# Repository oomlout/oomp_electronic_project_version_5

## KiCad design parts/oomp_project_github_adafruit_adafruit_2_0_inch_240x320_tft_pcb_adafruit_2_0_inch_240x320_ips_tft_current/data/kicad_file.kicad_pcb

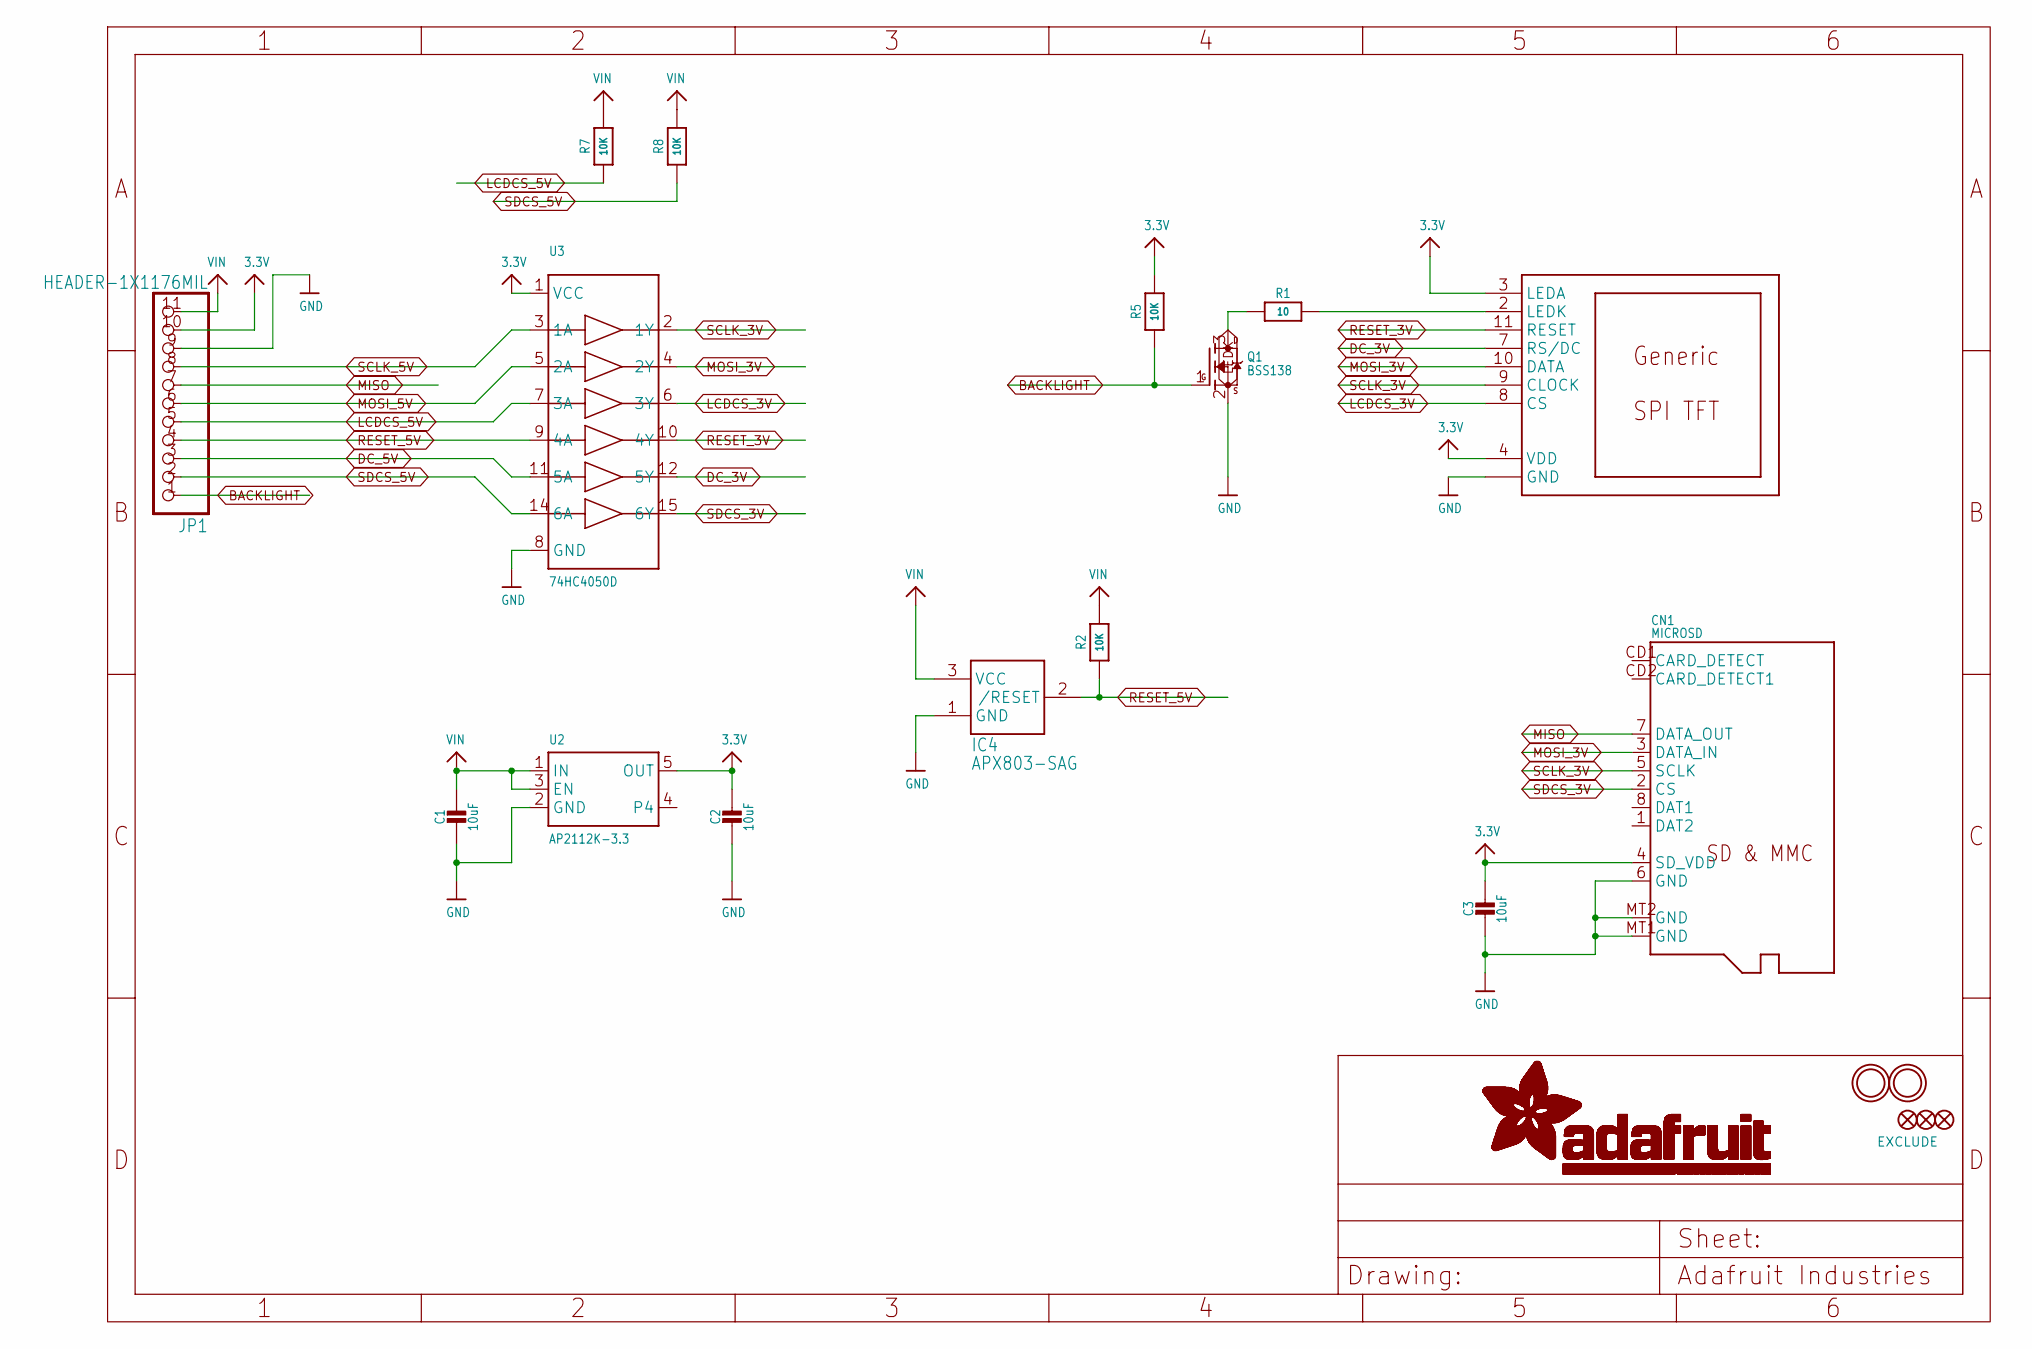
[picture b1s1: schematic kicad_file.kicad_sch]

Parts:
C1, C2, C3: 10uF; 0805-NO
CN1: MICROSD
DISP1: DISP_LCD_GENERIC_SPI_2.0IN_240X320; TFT_2.0IN_240X320_12P
FID1, FID2, FID3: FIDUCIAL_1MM
IC4: APX803-SAG; SOT23
JP1: HEADER-1X1176MIL; 1X11_ROUND_76
Q1: BSS138; SOT23-R
R1: 10; 0805-NO
R2, R5, R7, R8: 10K; 0805-NO
U2: AP2112K-3.3; SOT23-5
U3: 74HC4050D; SOIC16
U$3, U$4: MOUNTINGHOLE2.5; MOUNTINGHOLE_2.5_PLATED

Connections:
3.3V: C2.1, C3.1, CN1.4 (SD_VDD), DISP1.3 (LEDA), DISP1.4 (VDD), JP1.10, R5.2, U2.5 (OUT), U3.1 (VCC)
BACKLIGHT: JP1.1, Q1.1 (G), R5.1
DC_3V: DISP1.7 (RS/DC), U3.12 (5Y)
DC_5V: JP1.3, U3.11 (5A)
GND: C1.2, C2.2, C3.2, CN1.6 (GND), CN1.MT1 (GND), CN1.MT2 (GND), DISP1.1 (GND), DISP1.5 (GND), DISP1.6 (GND), DISP1.12 (GND), IC4.1 (GND), JP1.9, Q1.2 (S), U2.2 (GND), U3.8 (GND)
LCDCS_3V: DISP1.8 (CS), U3.6 (3Y)
LCDCS_5V: JP1.5, R7.1, U3.7 (3A)
LEDK: Q1.3 (D), R1.1
MISO: CN1.7 (DATA_OUT), JP1.7
MOSI_3V: CN1.3 (DATA_IN), DISP1.10 (DATA), U3.4 (2Y)
MOSI_5V: JP1.6, U3.5 (2A)
unnamed: DISP1.2 (LEDK), R1.2
RESET_3V: DISP1.11 (RESET), U3.10 (4Y)
RESET_5V: IC4.2 (/RESET), JP1.4, R2.1, U3.9 (4A)
SCLK_3V: CN1.5 (SCLK), DISP1.9 (CLOCK), U3.2 (1Y)
SCLK_5V: JP1.8, U3.3 (1A)
SDCS_3V: CN1.2 (CS), U3.15 (6Y)
SDCS_5V: JP1.2, R8.1, U3.14 (6A)
VIN: C1.1, IC4.3 (VCC), JP1.11, R2.2, R7.2, R8.2, U2.1 (IN), U2.3 (EN)

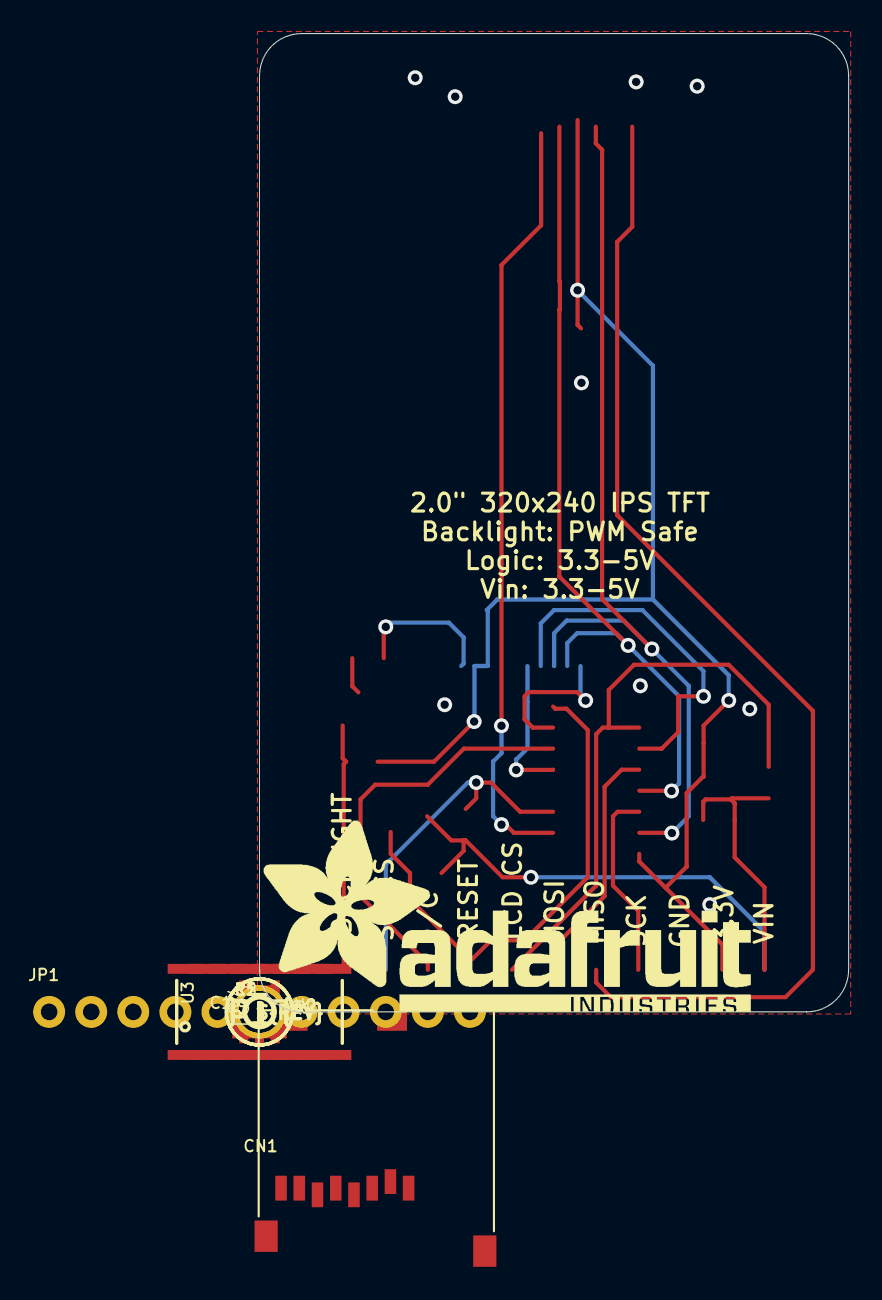
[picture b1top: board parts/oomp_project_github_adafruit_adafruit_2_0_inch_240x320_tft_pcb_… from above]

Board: 2 copper layers, 35.6 x 59.1 mm, 22 parts (1 on the bottom side), 19 nets.

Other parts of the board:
U$20: ADAFRUIT_TEXT_30MM
U$24: PCBFEAT-REV-040

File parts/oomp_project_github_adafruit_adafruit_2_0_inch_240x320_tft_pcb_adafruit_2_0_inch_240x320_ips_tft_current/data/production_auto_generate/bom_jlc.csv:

Comment,Designator,Footprint,LCSC Part #
,JP1,Adafruit 2.0 inch 240x320 IPS TFT-import-fps:1X11_ROUND_76,C2894934
,U$20,Adafruit 2.0 inch 240x320 IPS TFT-import-fps:ADAFRUIT_TEXT_30MM,
,CN1,Adafruit 2.0 inch 240x320 IPS TFT-import-fps:MICROSD,
,U$24,Adafruit 2.0 inch 240x320 IPS TFT-import-fps:PCBFEAT-REV-040,
10,R1,Adafruit 2.0 inch 240x320 IPS TFT-import-fps:0805-NO,C17415
10K,"R2,R5,R7,R8",Adafruit 2.0 inch 240x320 IPS TFT-import-fps:0805-NO,C17414
10uF,"C1,C2,C3",Adafruit 2.0 inch 240x320 IPS TFT-import-fps:0805-NO,
74HC4050D,U3,Adafruit 2.0 inch 240x320 IPS TFT-import-fps:SOIC16,
AP2112K-3.3,U2,Adafruit 2.0 inch 240x320 IPS TFT-import-fps:SOT23-5,
APX803-SAG,IC4,Adafruit 2.0 inch 240x320 IPS TFT-import-fps:SOT23,
BSS138,Q1,Adafruit 2.0 inch 240x320 IPS TFT-import-fps:SOT23-R,C52895
DISP_LCD_GENERIC_SPI_2.0IN_240X320,DISP1,Adafruit 2.0 inch 240x320 IPS TFT-import-fps:TFT_2.0IN_240X320_12P,

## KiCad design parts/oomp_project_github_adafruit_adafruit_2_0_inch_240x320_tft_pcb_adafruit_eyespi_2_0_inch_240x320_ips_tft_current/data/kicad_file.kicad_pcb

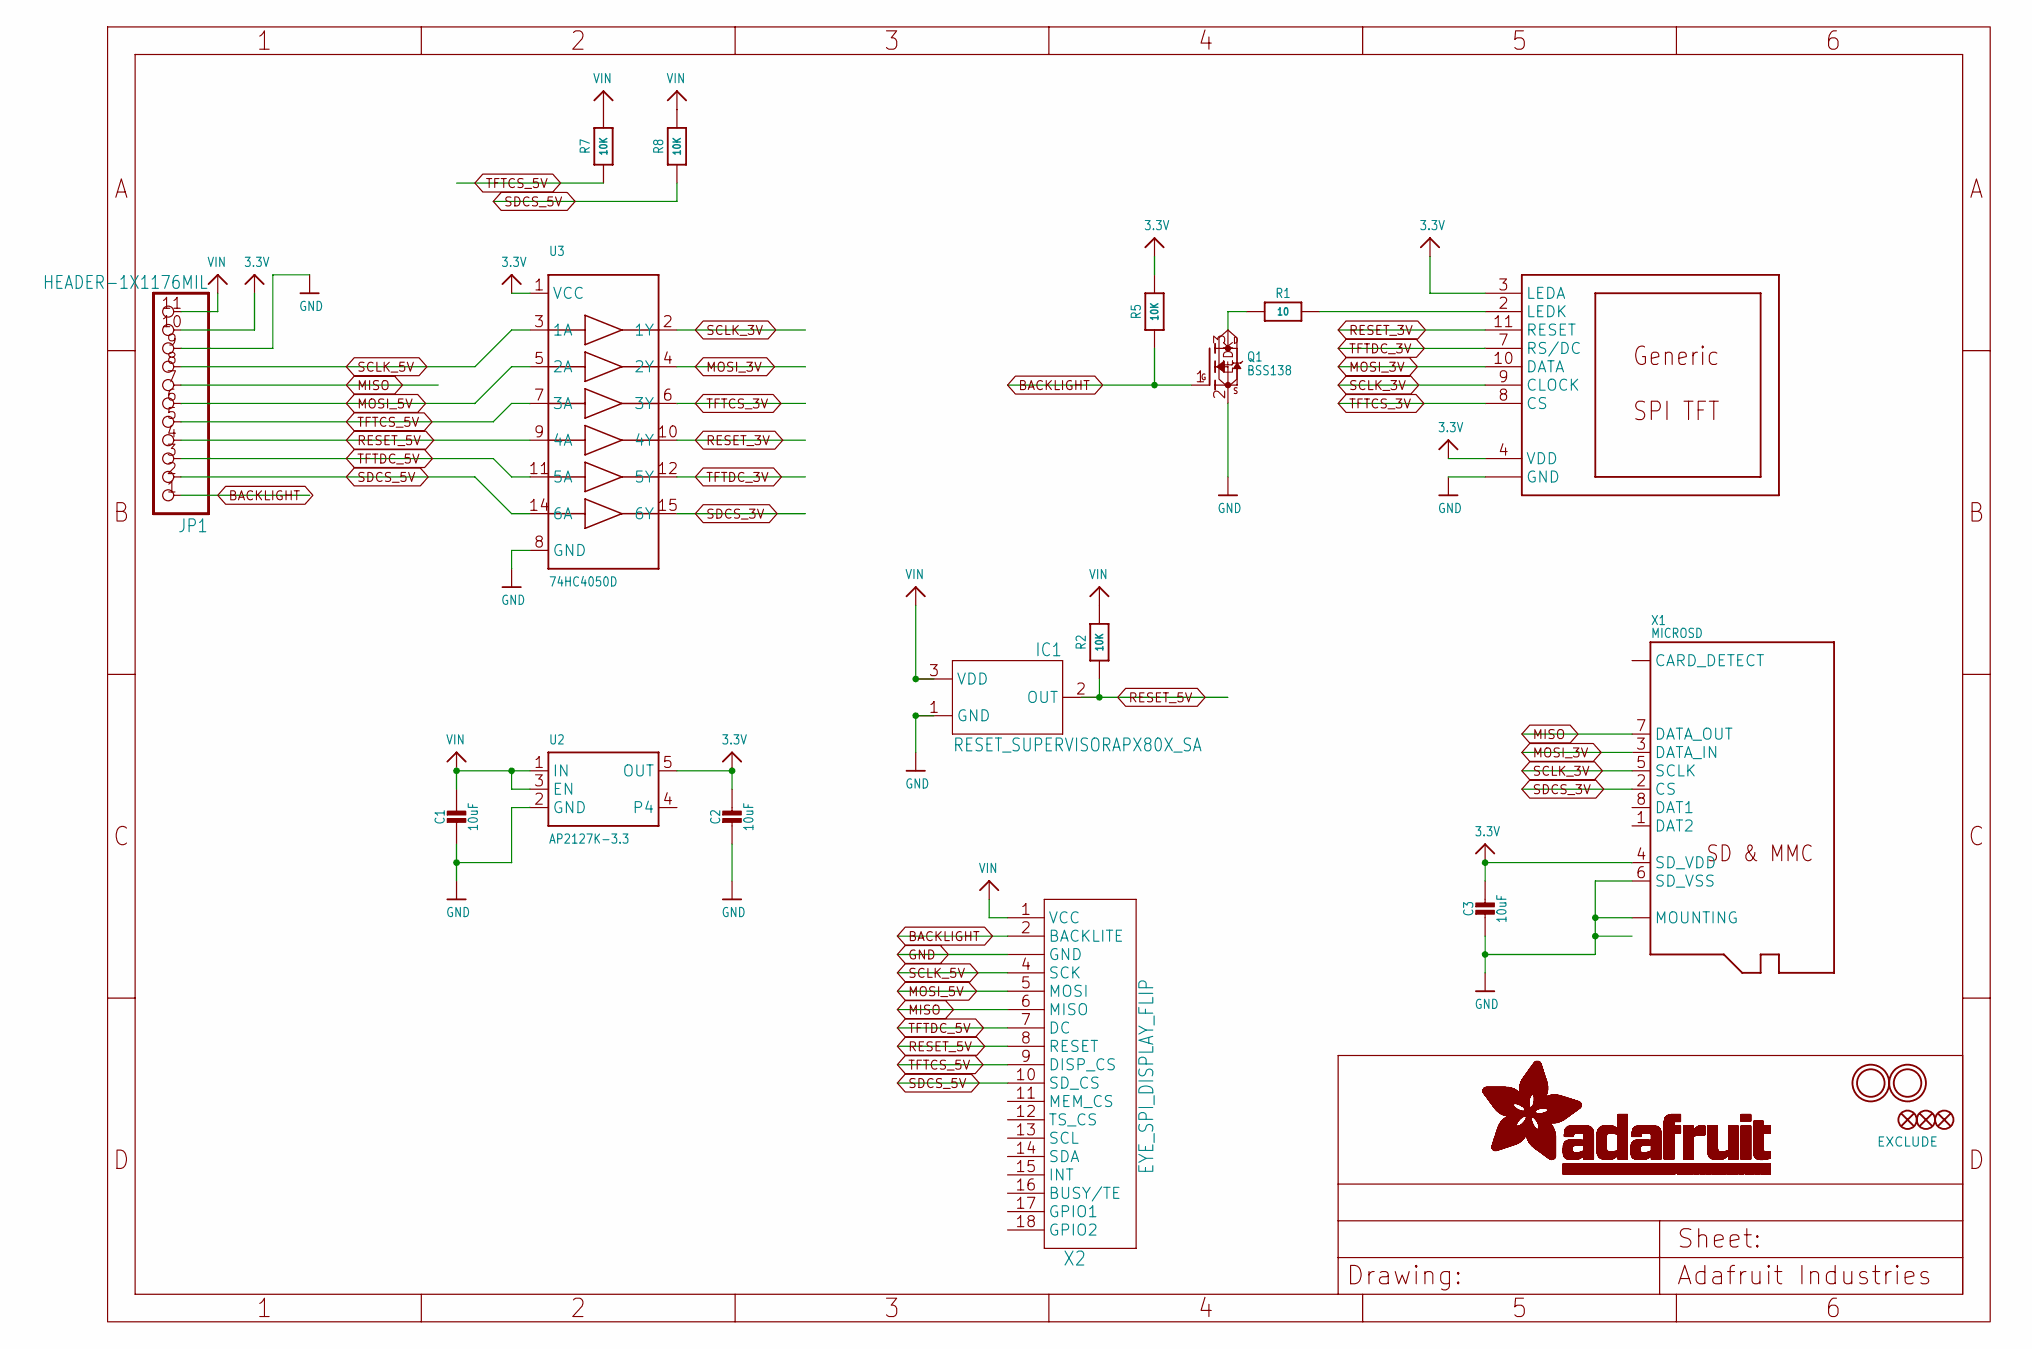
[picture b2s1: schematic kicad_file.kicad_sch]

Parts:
C1, C2, C3: 10uF; 0805-NO
DISP1: DISP_LCD_GENERIC_SPI_2.0IN_240X320; TFT_2.0IN_240X320_12P
FID1, FID2, FID3: FIDUCIAL_1MM
IC1: RESET_SUPERVISORAPX80X_SA; SOT23-WIDE
JP1: HEADER-1X1176MIL; 1X11_ROUND_76
Q1: BSS138; SOT23-R
R1: 10; 0805-NO
R2, R5, R7, R8: 10K; 0805-NO
U2: AP2127K-3.3; SOT23-5; JLC_ROTATION 270
U3: 74HC4050D; SOIC16
U$3, U$4: MOUNTINGHOLE2.5; MOUNTINGHOLE_2.5_PLATED
X1: MICROSD; JLC_ROTATION 90
X2: EYE_SPI_DISPLAY_FLIP; EYE_SPI_DISPLAY_BOTCONTACT; LCSC C2856802

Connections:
3.3V: C2.1, C3.1, DISP1.3 (LEDA), DISP1.4 (VDD), JP1.10, R5.2, U2.5 (OUT), U3.1 (VCC), X1.4 (SD_VDD)
BACKLIGHT: JP1.1, Q1.1 (G), R5.1, X2.2 (BACKLITE)
GND: C1.2, C2.2, C3.2, DISP1.1 (GND), DISP1.5 (GND), DISP1.6 (GND), DISP1.12 (GND), IC1.1 (GND), JP1.9, Q1.2 (S), U2.2 (GND), U3.8 (GND), X1.6 (SD_VSS), X1.MT1 (MOUNTING), X1.MT2 (MOUNTING), X2.3 (GND), X2.SUPPORT1 (GND), X2.SUPPORT2 (GND)
LEDK: Q1.3 (D), R1.1
MISO: JP1.7, X1.7 (DATA_OUT), X2.6 (MISO)
MOSI_3V: DISP1.10 (DATA), U3.4 (2Y), X1.3 (DATA_IN)
MOSI_5V: JP1.6, U3.5 (2A), X2.5 (MOSI)
unnamed: DISP1.2 (LEDK), R1.2
RESET_3V: DISP1.11 (RESET), U3.10 (4Y)
RESET_5V: IC1.2 (OUT), JP1.4, R2.1, U3.9 (4A), X2.8 (RESET)
SCLK_3V: DISP1.9 (CLOCK), U3.2 (1Y), X1.5 (SCLK)
SCLK_5V: JP1.8, U3.3 (1A), X2.4 (SCK)
SDCS_3V: U3.15 (6Y), X1.2 (CS)
SDCS_5V: JP1.2, R8.1, U3.14 (6A), X2.10 (SD_CS)
TFTCS_3V: DISP1.8 (CS), U3.6 (3Y)
TFTCS_5V: JP1.5, R7.1, U3.7 (3A), X2.9 (DISP_CS)
TFTDC_3V: DISP1.7 (RS/DC), U3.12 (5Y)
TFTDC_5V: JP1.3, U3.11 (5A), X2.7 (DC)
VIN: C1.1, IC1.3 (VDD), JP1.11, R2.2, R7.2, R8.2, U2.1 (IN), U2.3 (EN), X2.1 (VCC)

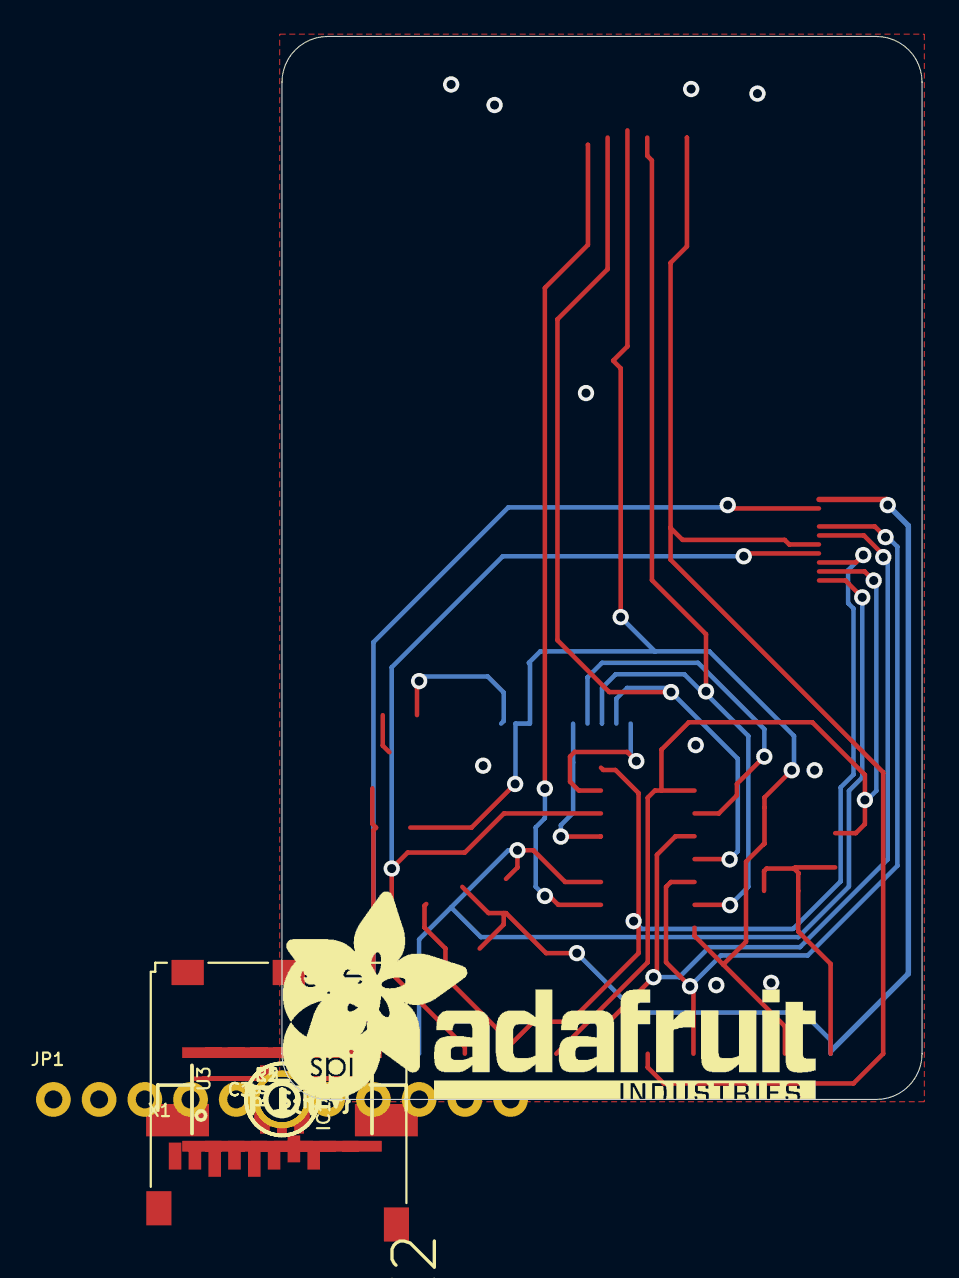
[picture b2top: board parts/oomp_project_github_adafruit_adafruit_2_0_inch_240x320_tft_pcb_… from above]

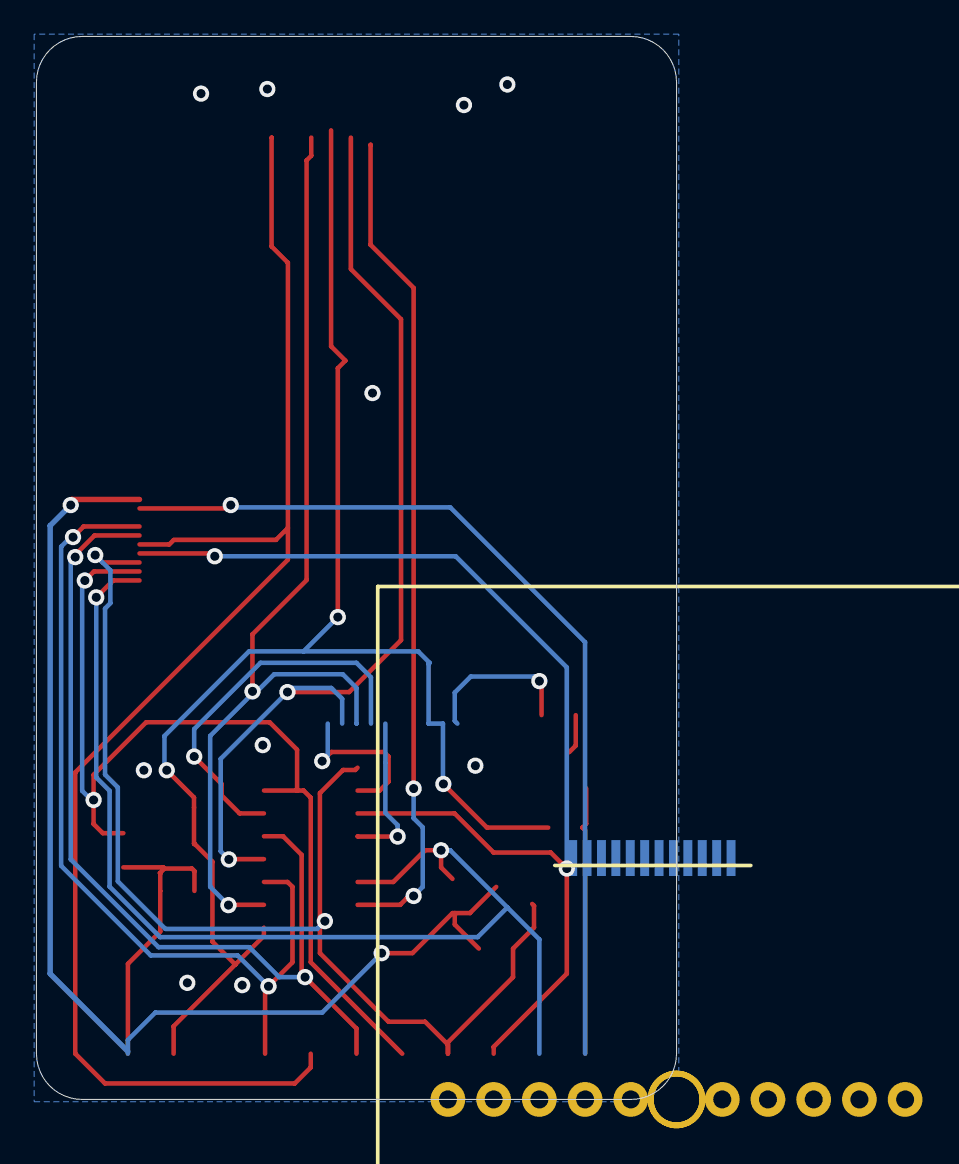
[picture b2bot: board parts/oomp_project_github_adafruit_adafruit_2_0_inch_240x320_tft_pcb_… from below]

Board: 2 copper layers, 35.6 x 59.1 mm, 48 parts (13 on the bottom side), 19 nets.

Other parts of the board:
PLABEL0: PLABEL0
PLABEL1: PLABEL1
PLABEL2: PLABEL2
PLABEL3: PLABEL3
PLABEL4: PLABEL4
PLABEL5: PLABEL5
PLABEL6: PLABEL6
PLABEL7: PLABEL7
PLABEL8: PLABEL8
PLABEL9: PLABEL9
PLABEL10: PLABEL10
PLABEL11: PLABEL11
PLABEL12: PLABEL12
PLABEL13: PLABEL13
PLABEL14: PLABEL14
PLABEL15: PLABEL15
PLABEL16: PLABEL16
PLABEL17: PLABEL17
PLABEL18: PLABEL18
PLABEL19: PLABEL19
PLABEL20: PLABEL20
PLABEL21: PLABEL21
PLABEL22: PLABEL22
PLABEL23: PLABEL23
U$20: ADAFRUIT_TEXT_30MM
U$24: PCBFEAT-REV-040
U$28: EYESPI_MINI_LOGO

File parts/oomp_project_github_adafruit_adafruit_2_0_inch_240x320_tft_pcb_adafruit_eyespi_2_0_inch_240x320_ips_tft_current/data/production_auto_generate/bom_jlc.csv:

Comment,Designator,Footprint,LCSC Part #
,JP1,Adafruit EYESPI 2.0 Inch 240x320 IPS TFT-import-fps:1X11_ROUND_76,C2894934
,U$20,Adafruit EYESPI 2.0 Inch 240x320 IPS TFT-import-fps:ADAFRUIT_TEXT_30MM,
,U$28,Adafruit EYESPI 2.0 Inch 240x320 IPS TFT-import-fps:EYESPI_MINI_LOGO,
,U$24,Adafruit EYESPI 2.0 Inch 240x320 IPS TFT-import-fps:PCBFEAT-REV-040,
,PLABEL0,Adafruit EYESPI 2.0 Inch 240x320 IPS TFT-import-fps:PLABEL0,
,PLABEL1,Adafruit EYESPI 2.0 Inch 240x320 IPS TFT-import-fps:PLABEL1,
,PLABEL10,Adafruit EYESPI 2.0 Inch 240x320 IPS TFT-import-fps:PLABEL10,
,PLABEL11,Adafruit EYESPI 2.0 Inch 240x320 IPS TFT-import-fps:PLABEL11,
,PLABEL12,Adafruit EYESPI 2.0 Inch 240x320 IPS TFT-import-fps:PLABEL12,
,PLABEL13,Adafruit EYESPI 2.0 Inch 240x320 IPS TFT-import-fps:PLABEL13,
,PLABEL14,Adafruit EYESPI 2.0 Inch 240x320 IPS TFT-import-fps:PLABEL14,
,PLABEL15,Adafruit EYESPI 2.0 Inch 240x320 IPS TFT-import-fps:PLABEL15,
,PLABEL16,Adafruit EYESPI 2.0 Inch 240x320 IPS TFT-import-fps:PLABEL16,
,PLABEL17,Adafruit EYESPI 2.0 Inch 240x320 IPS TFT-import-fps:PLABEL17,
,PLABEL18,Adafruit EYESPI 2.0 Inch 240x320 IPS TFT-import-fps:PLABEL18,
,PLABEL19,Adafruit EYESPI 2.0 Inch 240x320 IPS TFT-import-fps:PLABEL19,
,PLABEL2,Adafruit EYESPI 2.0 Inch 240x320 IPS TFT-import-fps:PLABEL2,
,PLABEL20,Adafruit EYESPI 2.0 Inch 240x320 IPS TFT-import-fps:PLABEL20,
,PLABEL21,Adafruit EYESPI 2.0 Inch 240x320 IPS TFT-import-fps:PLABEL21,
,PLABEL22,Adafruit EYESPI 2.0 Inch 240x320 IPS TFT-import-fps:PLABEL22,
,PLABEL23,Adafruit EYESPI 2.0 Inch 240x320 IPS TFT-import-fps:PLABEL23,
,PLABEL3,Adafruit EYESPI 2.0 Inch 240x320 IPS TFT-import-fps:PLABEL3,
,PLABEL4,Adafruit EYESPI 2.0 Inch 240x320 IPS TFT-import-fps:PLABEL4,
,PLABEL5,Adafruit EYESPI 2.0 Inch 240x320 IPS TFT-import-fps:PLABEL5,
,PLABEL6,Adafruit EYESPI 2.0 Inch 240x320 IPS TFT-import-fps:PLABEL6,
,PLABEL7,Adafruit EYESPI 2.0 Inch 240x320 IPS TFT-import-fps:PLABEL7,
,PLABEL8,Adafruit EYESPI 2.0 Inch 240x320 IPS TFT-import-fps:PLABEL8,
,PLABEL9,Adafruit EYESPI 2.0 Inch 240x320 IPS TFT-import-fps:PLABEL9,
10,R1,Adafruit EYESPI 2.0 Inch 240x320 IPS TFT-import-fps:0805-NO,C17415
10K,"R2,R5,R7,R8",Adafruit EYESPI 2.0 Inch 240x320 IPS TFT-import-fps:0805-NO,C17414
10uF,"C1,C2,C3",Adafruit EYESPI 2.0 Inch 240x320 IPS TFT-import-fps:0805-NO,
74HC4050D,U3,Adafruit EYESPI 2.0 Inch 240x320 IPS TFT-import-fps:SOIC16,
AP2127K-3.3,U2,Adafruit EYESPI 2.0 Inch 240x320 IPS TFT-import-fps:SOT23-5,
BSS138,Q1,Adafruit EYESPI 2.0 Inch 240x320 IPS TFT-import-fps:SOT23-R,C52895
DISP_LCD_GENERIC_SPI_2.0IN_240X320,DISP1,Adafruit EYESPI 2.0 Inch 240x320 IPS TFT-import-fps:TFT_2.0IN_240X320_12P,
EYE_SPI_DISPLAY_FLIP,X2,Adafruit EYESPI 2.0 Inch 240x320 IPS TFT-import-fps:EYE_SPI_DISPLAY_BOTCONTACT,
MICROSD,X1,Adafruit EYESPI 2.0 Inch 240x320 IPS TFT-import-fps:MICROSD,
RESET_SUPERVISORAPX80X_SA,IC1,Adafruit EYESPI 2.0 Inch 240x320 IPS TFT-import-fps:SOT23-WIDE,

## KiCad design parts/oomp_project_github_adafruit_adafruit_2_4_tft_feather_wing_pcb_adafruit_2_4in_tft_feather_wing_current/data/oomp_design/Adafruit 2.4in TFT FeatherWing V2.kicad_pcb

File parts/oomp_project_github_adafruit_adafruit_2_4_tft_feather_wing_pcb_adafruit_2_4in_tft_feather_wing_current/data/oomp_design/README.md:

# OOMP KiCad design copy

Open `Adafruit 2.4in TFT FeatherWing V2.kicad_pro` (or the `.kicad_pcb` / `.kicad_sch`) in KiCad. Local OOMP libraries are under `libraries/`. Original inputs are preserved in [../original/](../original/).

Only verified unchanged installed KiCad defaults were renamed. Modified, custom, unmatched and unavailable items remain unchanged. Soldering variants are never swapped during conversion. Existing pad coordinates, nets and UUIDs are preserved.

See [conversion_report.yaml](conversion_report.yaml) for every conversion and skip. Copy this directory before editing; regeneration refuses to overwrite edited design files.

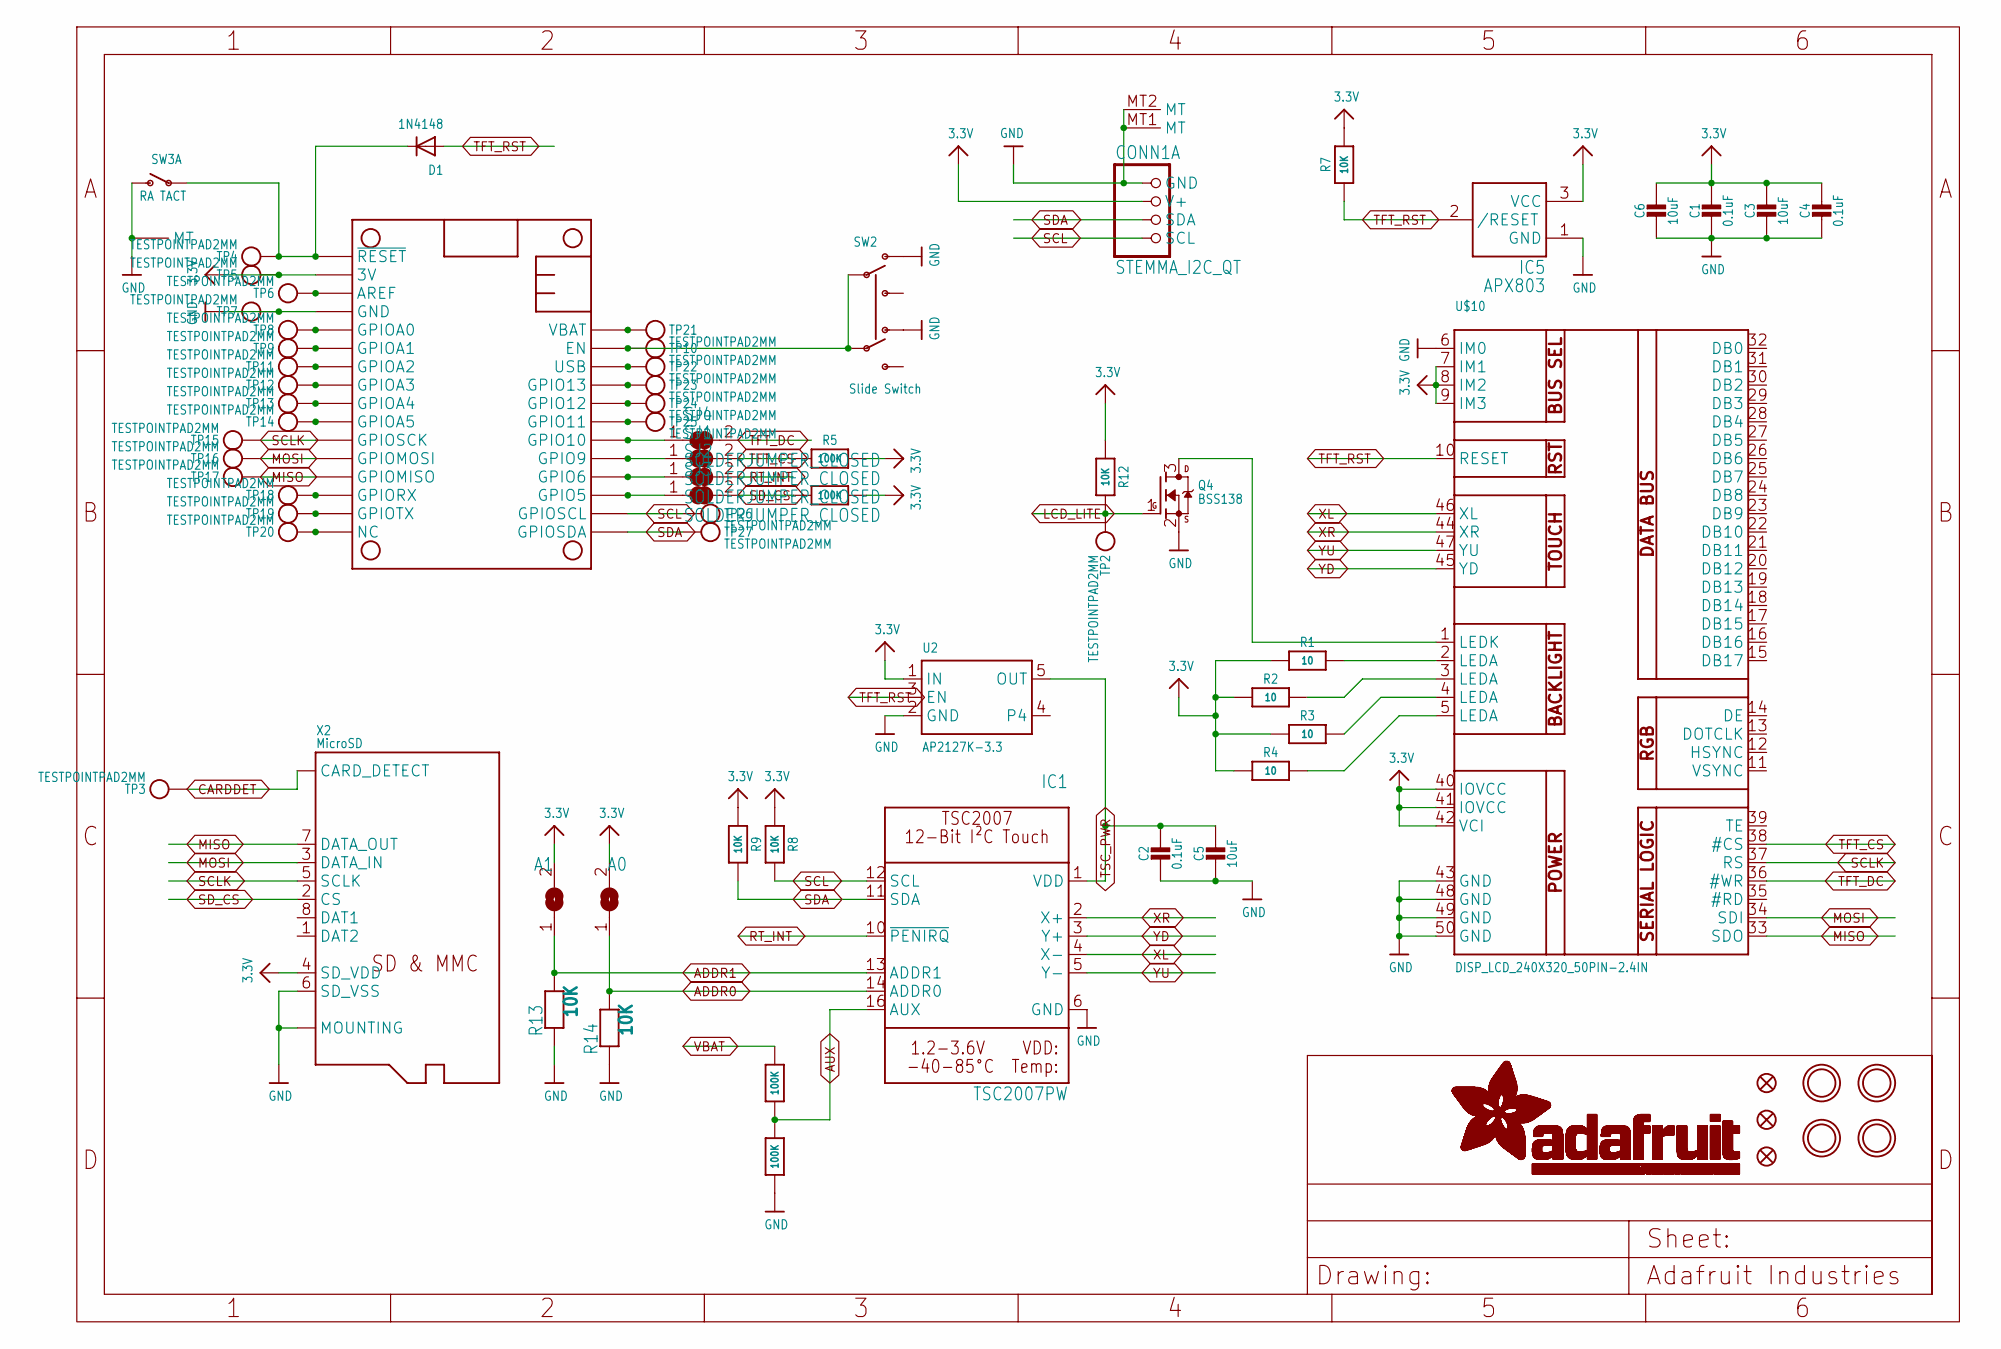
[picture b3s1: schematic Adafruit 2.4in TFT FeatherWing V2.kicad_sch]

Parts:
C1, C2, C4: 0.1uF; 0603-NO
C3, C5, C6: 10uF; 0805-NO
CONN1: STEMMA_I2C_QT; JST_SH4; LCSC C2845363
D1: 1N4148; SOD-323
FID1, FID2, FID3: FIDUCIAL_1MM
IC1: TSC2007PW; TSSOP16
IC5: APX803; SOT23
ICSP_CLK1: A1; SOLDERJUMPER_ARROW_NOPASTE
ICSP_CLK2: A0; SOLDERJUMPER_ARROW_NOPASTE
MS2: FEATHERWING_SMTDUAL; FEATHERWING_SMT2
Q4: BSS138; SOT23-WIDE
R1, R2, R3, R4: 10; 0603-NO
R5, R6, R10, R11: 100K; 0603-NO
R7, R8, R9, R12, R13, R14: 10K; 0603-NO
SJ1, SJ2, SJ3, SJ4: SOLDERJUMPER_CLOSED; SOLDERJUMPER_CLOSEDWIRE
SW2: Slide Switch; EG1390; LCSC C2837066
SW3: RA TACT; SPST_TACTILE_RA; LCSC C778159
TP2, TP3, TP4, TP5, TP6, TP7, TP8, TP9, TP10, TP11, TP12, TP13, TP14, TP15, TP16, TP17, TP18, TP19, TP20, TP21, TP22, TP23, TP24, TP25, TP26, TP27: TESTPOINTPAD2MM; TESTPOINT_PAD_2MM
U2: AP2127K-3.3; SOT23-5; JLC_ROTATION 270
U$9, U$11, U$15, U$17: MOUNTINGHOLE2.5; MOUNTINGHOLE_2.5_PLATED
U$10: DISP_LCD_240X320_50PIN-2.4IN; TFT_2.4IN_240X320_50PIN
X2: MicroSD; MICROSD; JLC_ROTATION 90

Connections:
3.3V: C1.1, C3.1, C4.1, C6.1, CONN1.2 (V+), IC5.3 (VCC), ICSP_CLK1.2, ICSP_CLK2.2, MS2.2 (3V), MS2.2' (3V), R1.1, R2.1, R3.1, R4.1, R5.2, R6.2, R7.2, R8.1, R9.1, R12.1, TP5.P$1, U2.1 (IN), U$10.7 (IM1), U$10.8 (IM2), U$10.9 (IM3), U$10.40 (IOVCC), U$10.41 (IOVCC), U$10.42 (VCI), X2.4 (SD_VDD)
A: MS2.5 (GPIOA0), MS2.5' (GPIOA0), TP8.P$1
ADDR0: IC1.14 (ADDR0), ICSP_CLK2.1, R14.2
ADDR1: IC1.13 (ADDR1), ICSP_CLK1.1, R13.2
AREF: MS2.3 (AREF), MS2.3' (AREF), TP6.P$1
AUX: IC1.16 (AUX), R10.1, R11.2
B: MS2.6 (GPIOA1), MS2.6' (GPIOA1), TP9.P$1
C: MS2.7 (GPIOA2), MS2.7' (GPIOA2), TP11.P$1
CARDDET: TP3.P$1, X2.CD1 (CARD_DETECT), X2.CD2 (CARD_DETECT)
D: MS2.8 (GPIOA3), MS2.8' (GPIOA3), TP12.P$1
E: MS2.9 (GPIOA4), MS2.9' (GPIOA4), TP13.P$1
EN: MS2.27 (EN), MS2.27' (EN), SW2.P1, SW2.P2, TP10.P$1
F: MS2.10 (GPIOA5), MS2.10' (GPIOA5), TP14.P$1
G: MS2.16 (NC), MS2.16' (NC), TP20.P$1
GND: C1.2, C2.2, C3.2, C4.2, C5.2, C6.2, CONN1.1 (GND), CONN1.MT1 (MT), CONN1.MT2 (MT), IC1.6 (GND), IC5.1 (GND), MS2.4 (GND), MS2.4' (GND), Q4.2 (S), R11.1, R13.1, R14.1, SW2.O1, SW2.O2, SW3.2 (S), SW3.MT1 (MT), SW3.MT2 (MT), TP7.P$1, U2.2 (GND), U$10.6 (IM0), U$10.43 (GND), U$10.48 (GND), U$10.49 (GND), U$10.50 (GND), X2.6 (SD_VSS), X2.MT1 (MOUNTING), X2.MT2 (MOUNTING)
H: MS2.19 (GPIO5), MS2.19' (GPIO5), SJ3.1
I: MS2.20 (GPIO6), MS2.20' (GPIO6), SJ2.1
J: MS2.21 (GPIO9), MS2.21' (GPIO9), SJ1.1
K: MS2.22 (GPIO10), MS2.22' (GPIO10), SJ4.1
L: MS2.23 (GPIO11), MS2.23' (GPIO11), TP25.P$1
LCD_LITE: Q4.1 (G), R12.2, TP2.P$1
M: MS2.24 (GPIO12), MS2.24' (GPIO12), TP24.P$1
MISO: MS2.13 (GPIOMISO), MS2.13' (GPIOMISO), TP17.P$1, U$10.33 (SDO), X2.7 (DATA_OUT)
MOSI: MS2.12 (GPIOMOSI), MS2.12' (GPIOMOSI), TP16.P$1, U$10.34 (SDI), X2.3 (DATA_IN)
N: MS2.25 (GPIO13), MS2.25' (GPIO13), TP23.P$1
unnamed: R4.2, U$10.5 (LEDA)
unnamed: R1.2, U$10.2 (LEDA)
unnamed: R2.2, U$10.3 (LEDA)
unnamed: R3.2, U$10.4 (LEDA)
unnamed: Q4.3 (D), U$10.1 (LEDK)
RT_INT: IC1.10 (~PENIRQ), SJ2.2
RX: MS2.14 (GPIORX), MS2.14' (GPIORX), TP18.P$1
SCL: CONN1.4 (SCL), IC1.12 (SCL), MS2.18 (GPIOSCL), MS2.18' (GPIOSCL), R8.2, TP26.P$1
SCLK: MS2.11 (GPIOSCK), MS2.11' (GPIOSCK), TP15.P$1, U$10.37 (RS), X2.5 (SCLK)
SDA: CONN1.3 (SDA), IC1.11 (SDA), MS2.17 (GPIOSDA), MS2.17' (GPIOSDA), R9.2, TP27.P$1
SD_CS: R6.1, SJ3.2, X2.2 (CS)
TFT_CS: R5.1, SJ1.2, U$10.38 (#CS)
TFT_DC: SJ4.2, U$10.36 (#WR)
TFT_RST: D1.A, IC5.2 (/RESET), R7.1, U2.3 (EN), U$10.10 (RESET)
TSC_PWR: C2.1, C5.1, IC1.1 (VDD), U2.5 (OUT)
TX: MS2.15 (GPIOTX), MS2.15' (GPIOTX), TP19.P$1
USB: MS2.26 (USB), MS2.26' (USB), TP22.P$1
XL: IC1.4 (X-), U$10.46 (XL)
XR: IC1.2 (X+), U$10.44 (XR)
YD: IC1.3 (Y+), U$10.45 (YD)
YU: IC1.5 (Y-), U$10.47 (YU)
~RESET: D1.C, MS2.1 (~RESET), MS2.1' (~RESET), SW3.1, TP4.P$1

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
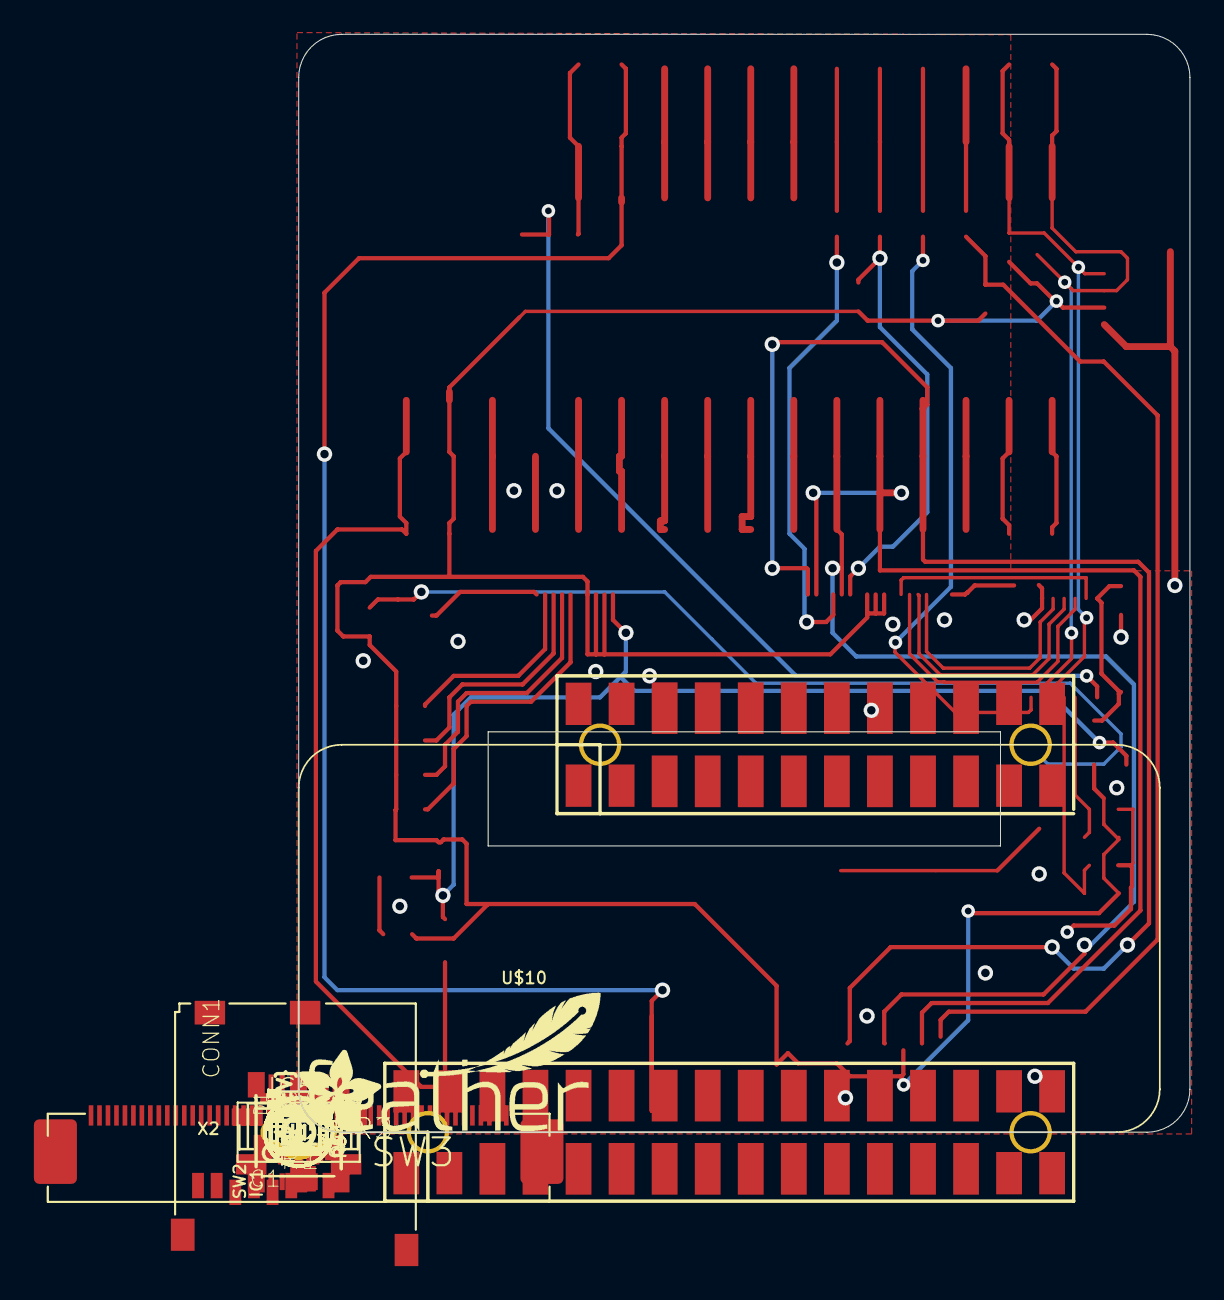
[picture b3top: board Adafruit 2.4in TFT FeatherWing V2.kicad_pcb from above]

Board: 16 copper layers, 52.6 x 64.8 mm, 87 parts (1 on the bottom side), 48 nets.

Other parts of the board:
PLABEL0: PLABEL0
PLABEL1: PLABEL1
PLABEL2: PLABEL2
PLABEL3: PLABEL3
PLABEL4: PLABEL4
PLABEL5: PLABEL5
PLABEL6: PLABEL6
PLABEL7: PLABEL7
PLABEL8: PLABEL8
PLABEL9: PLABEL9
PLABEL10: PLABEL10
PLABEL11: PLABEL11
PLABEL12: PLABEL12
PLABEL13: PLABEL13
U$29: FEATHERLOGO_MED
U$30: ADAFRUIT_5MM
U$34: PCBFEAT-REV-040

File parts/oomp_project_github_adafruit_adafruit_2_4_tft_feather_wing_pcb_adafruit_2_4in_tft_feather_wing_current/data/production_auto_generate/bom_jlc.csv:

Comment,Designator,Footprint,LCSC Part #
,U$30,Adafruit 2.4in TFT FeatherWing V2-import-fps:ADAFRUIT_5MM,
,U$29,Adafruit 2.4in TFT FeatherWing V2-import-fps:FEATHERLOGO_MED,
,U$34,Adafruit 2.4in TFT FeatherWing V2-import-fps:PCBFEAT-REV-040,
,PLABEL0,Adafruit 2.4in TFT FeatherWing V2-import-fps:PLABEL0,
,PLABEL1,Adafruit 2.4in TFT FeatherWing V2-import-fps:PLABEL1,
,PLABEL10,Adafruit 2.4in TFT FeatherWing V2-import-fps:PLABEL10,
,PLABEL11,Adafruit 2.4in TFT FeatherWing V2-import-fps:PLABEL11,
,PLABEL12,Adafruit 2.4in TFT FeatherWing V2-import-fps:PLABEL12,
,PLABEL13,Adafruit 2.4in TFT FeatherWing V2-import-fps:PLABEL13,
,PLABEL2,Adafruit 2.4in TFT FeatherWing V2-import-fps:PLABEL2,
,PLABEL3,Adafruit 2.4in TFT FeatherWing V2-import-fps:PLABEL3,
,PLABEL4,Adafruit 2.4in TFT FeatherWing V2-import-fps:PLABEL4,
,PLABEL5,Adafruit 2.4in TFT FeatherWing V2-import-fps:PLABEL5,
,PLABEL6,Adafruit 2.4in TFT FeatherWing V2-import-fps:PLABEL6,
,PLABEL7,Adafruit 2.4in TFT FeatherWing V2-import-fps:PLABEL7,
,PLABEL8,Adafruit 2.4in TFT FeatherWing V2-import-fps:PLABEL8,
,PLABEL9,Adafruit 2.4in TFT FeatherWing V2-import-fps:PLABEL9,
,"TP2,TP3,TP4,TP5,TP6,TP7,TP8,TP9,TP10,TP11,TP12,TP13,TP14,TP15,TP16,TP17,TP18,TP19,TP20,TP21,TP22,TP23,TP24,TP25,TP26,TP27",Adafruit 2.4in TFT FeatherWing V2-import-fps:TESTPOINT_PAD_2MM,
0.1uF,"C1,C2,C4",Adafruit 2.4in TFT FeatherWing V2-import-fps:0603-NO,C14663
10,"R1,R2,R3,R4",Adafruit 2.4in TFT FeatherWing V2-import-fps:0603-NO,C22859
100K,"R5,R6,R10,R11",Adafruit 2.4in TFT FeatherWing V2-import-fps:0603-NO,C25803
10K,"R7,R8,R9,R12,R13,R14",Adafruit 2.4in TFT FeatherWing V2-import-fps:0603-NO,C98220
10uF,"C3,C5,C6",Adafruit 2.4in TFT FeatherWing V2-import-fps:0805-NO,
1N4148,D1,Adafruit 2.4in TFT FeatherWing V2-import-fps:SOD-323,
A0,ICSP_CLK2,Adafruit 2.4in TFT FeatherWing V2-import-fps:SOLDERJUMPER_ARROW_NOPASTE,
A1,ICSP_CLK1,Adafruit 2.4in TFT FeatherWing V2-import-fps:SOLDERJUMPER_ARROW_NOPASTE,
AP2127K-3.3,U2,Adafruit 2.4in TFT FeatherWing V2-import-fps:SOT23-5,
APX803,IC5,Adafruit 2.4in TFT FeatherWing V2-import-fps:SOT23,
BSS138,Q4,Adafruit 2.4in TFT FeatherWing V2-import-fps:SOT23-WIDE,C52895
DISP_LCD_240X320_50PIN-2.4IN,U$10,Adafruit 2.4in TFT FeatherWing V2-import-fps:TFT_2.4IN_240X320_50PIN,
FEATHERWING_SMTDUAL,MS2,Adafruit 2.4in TFT FeatherWing V2-import-fps:FEATHERWING_SMT2,
MicroSD,X2,Adafruit 2.4in TFT FeatherWing V2-import-fps:MICROSD,
RA TACT,SW3,Adafruit 2.4in TFT FeatherWing V2-import-fps:SPST_TACTILE_RA,
Slide Switch,SW2,Adafruit 2.4in TFT FeatherWing V2-import-fps:EG1390,
STEMMA_I2C_QT,CONN1,Adafruit 2.4in TFT FeatherWing V2-import-fps:JST_SH4,C160404
TSC2007PW,IC1,Adafruit 2.4in TFT FeatherWing V2-import-fps:TSSOP16,
